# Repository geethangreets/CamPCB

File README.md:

# Hardware Development of Illumination and Sensor Board for Multispectral Cameras System 
This project is about hardware development for a vital sign detection device

This is a device that allows patients to take images of wounds at their homes with a higher frequency compared to typical hospital visits. The images would then be made available to their clinicians for continuous wound monitoring.

System Diagram:

3D rendering of the assembly:

Final PCB rendering front and back

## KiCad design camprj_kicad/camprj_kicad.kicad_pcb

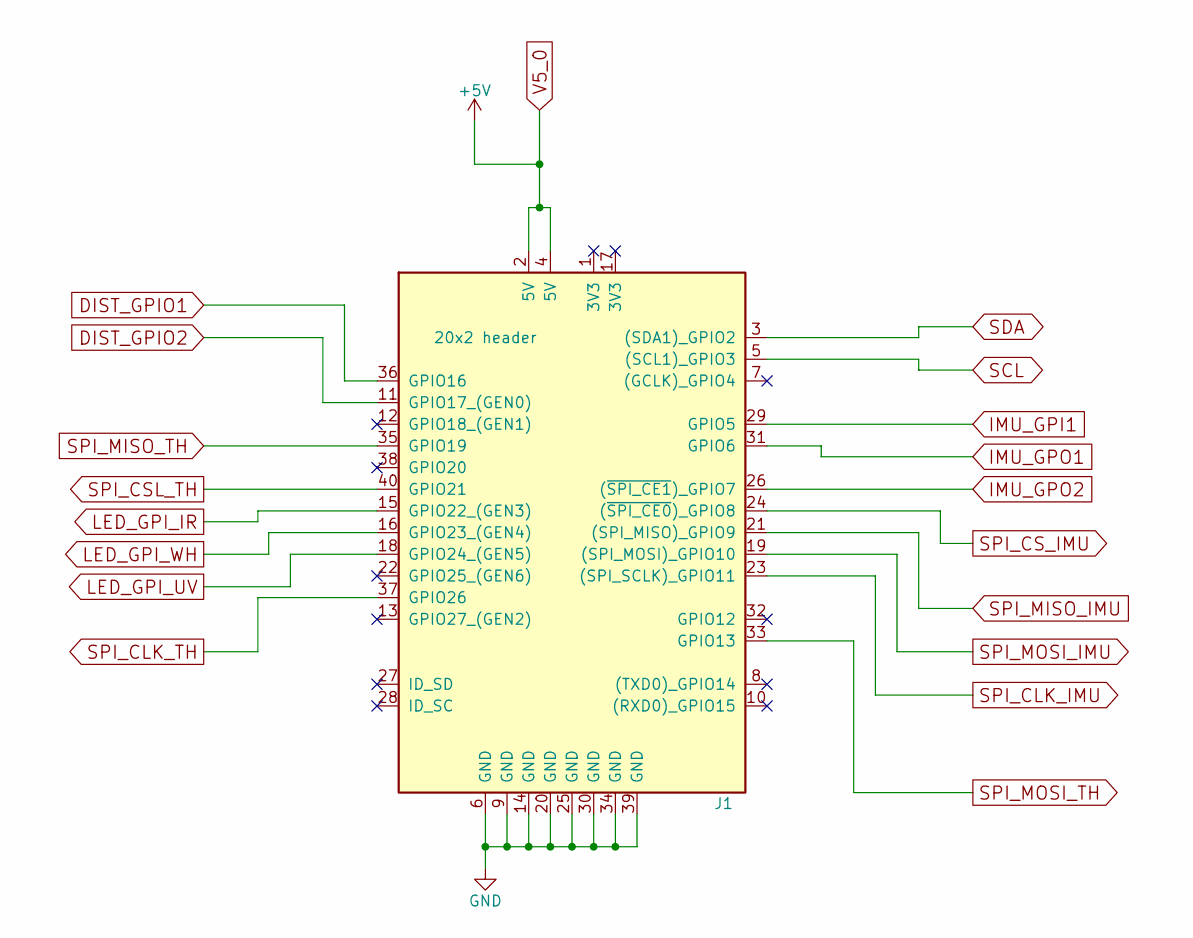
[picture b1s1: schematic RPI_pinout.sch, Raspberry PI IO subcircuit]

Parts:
J1: 20x2 header; Pin_Header_Straight_2x20_Pitch2.54mm; MPN ESQ-120-69-G-D-LL

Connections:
DIST_GPIO1: J1.36 (GPIO16); also elsewhere on the board
DIST_GPIO2: J1.11 (GPIO17_(GEN0)); also elsewhere on the board
GND: J1.6 (GND), J1.9 (GND), J1.14 (GND), J1.20 (GND), J1.25 (GND), J1.30 (GND), J1.34 (GND), J1.39 (GND); also elsewhere on the board
IMU_GPI1: J1.29 (GPIO5); also elsewhere on the board
IMU_GPO1: J1.31 (GPIO6); also elsewhere on the board
IMU_GPO2: J1.26 ((~SPI_CE1~)_GPIO7); also elsewhere on the board
LED_GPI_IR: J1.15 (GPIO22_(GEN3)); also elsewhere on the board
LED_GPI_UV: J1.18 (GPIO24_(GEN5)); also elsewhere on the board
LED_GPI_WH: J1.16 (GPIO23_(GEN4)); also elsewhere on the board
SCL: J1.5 ((SCL1)_GPIO3); also elsewhere on the board
SDA: J1.3 ((SDA1)_GPIO2); also elsewhere on the board
SPI_CLK_IMU: J1.23 ((SPI_SCLK)_GPIO11); also elsewhere on the board
SPI_CLK_TH: J1.37 (GPIO26); also elsewhere on the board
SPI_CSL_TH: J1.40 (GPIO21); also elsewhere on the board
SPI_CS_IMU: J1.24 ((~SPI_CE0~)_GPIO8); also elsewhere on the board
SPI_MISO_IMU: J1.21 ((SPI_MISO)_GPIO9); also elsewhere on the board
SPI_MISO_TH: J1.35 (GPIO19); also elsewhere on the board
SPI_MOSI_IMU: J1.19 ((SPI_MOSI)_GPIO10); also elsewhere on the board
SPI_MOSI_TH: J1.33 (GPIO13); also elsewhere on the board
V5_0: J1.2 (5V), J1.4 (5V); also elsewhere on the board

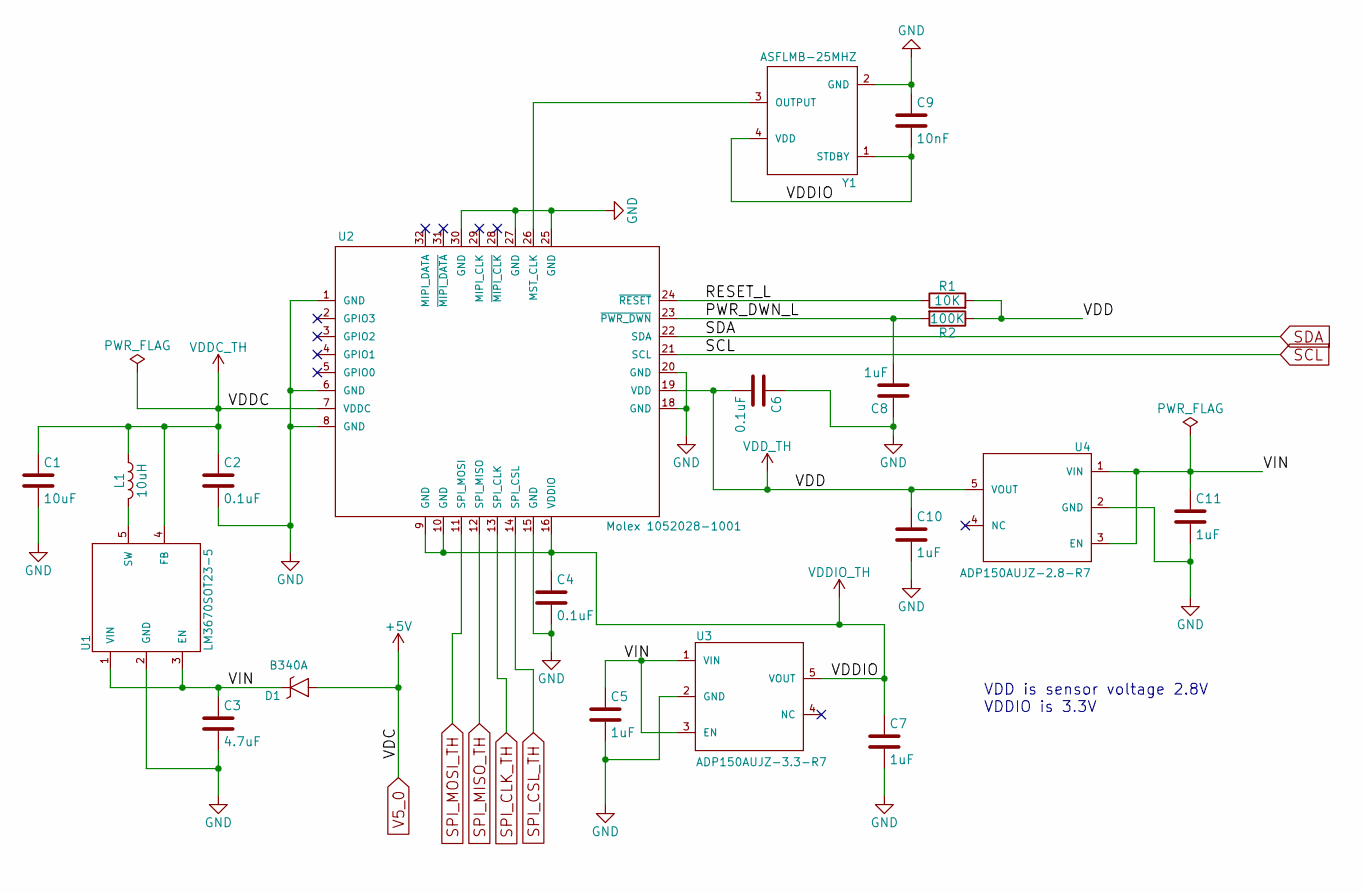
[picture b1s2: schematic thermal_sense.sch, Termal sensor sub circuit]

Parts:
C1: 10uF; C_0603_HandSoldering
C2, C4, C6: 0.1uF; C_0603_HandSoldering
C3: 4.7uF; C_0603_HandSoldering
C5, C7, C8, C10, C11: 1uF; C_0603_HandSoldering
C9: 10nF; C_0603_HandSoldering
D1: B340A; D_SMA_Handsoldering_AC; MPN B340A-13-F
L1: 10uH; L_1210_HandSoldering
R1: 10K; R_0603_HandSoldering
R2: 100K; R_0603_HandSoldering
U1: LM3670SOT23-5; SOT-23-5_HandSoldering; MPN LM3670MFX-ADJ/NOPB
U2: Molex 1052028-1001; 105028-1001; MPN 105028-1001
U3: ADP150AUJZ-3.3-R7; TSOT-23-5_HandSoldering; MPN ADP150AUJZ-3.3-R7
U4: ADP150AUJZ-2.8-R7; TSOT-23-5_HandSoldering; MPN ADP150AUJZ-2.8-R7
Y1: ASFLMB-25MHZ; 5X3.2-CRYSTAL; MPN ASFLMB-25.000MHZ-LC-T

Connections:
/thermal_sense/PWR_DWN_L: C8.2, R2.2, U2.23 (~PWR_DWN)
/thermal_sense/RESET_L: R1.1, U2.24 (~RESET)
/thermal_sense/VIN: C3.1, C5.1, C11.1, D1.C, U1.1 (VIN), U1.3 (EN), U3.1 (VIN), U3.3 (EN), U4.1 (VIN), U4.3 (EN)
GND: C1.2, C2.2, C3.2, C4.2, C5.2, C6.1, C7.2, C8.1, C9.1, C10.2, C11.2, U1.2 (GND), U2.1 (GND), U2.6 (GND), U2.8 (GND), U2.15 (GND), U2.18 (GND), U2.20 (GND), U2.25 (GND), U2.27 (GND), U2.30 (GND), U3.2 (GND), U4.2 (GND), Y1.2 (GND); also elsewhere on the board
unnamed: L1.2, U1.5 (SW)
unnamed: U2.26 (MST_CLK), Y1.3 (OUTPUT)
SCL: U2.21 (SCL); also elsewhere on the board
SDA: U2.22 (SDA); also elsewhere on the board
SPI_CLK_TH: U2.13 (SPI_CLK); also elsewhere on the board
SPI_CSL_TH: U2.14 (SPI_CSL); also elsewhere on the board
SPI_MISO_TH: U2.12 (SPI_MISO); also elsewhere on the board
SPI_MOSI_TH: U2.11 (SPI_MOSI); also elsewhere on the board
V5_0: D1.A; also elsewhere on the board
VDDC_TH: C1.1, C2.1, L1.1, U1.4 (FB), U2.7 (VDDC)
VDDIO_TH: C4.1, C7.1, C9.2, U2.9 (GND), U2.10 (GND), U2.16 (VDDIO), U3.5 (VOUT), Y1.1 (STDBY), Y1.4 (VDD)
VDD_TH: C6.2, C10.1, R1.2, R2.1, U2.19 (VDD), U4.5 (VOUT)

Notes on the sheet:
VDD is sensor voltage 2.8V VDDIO is 3.3V

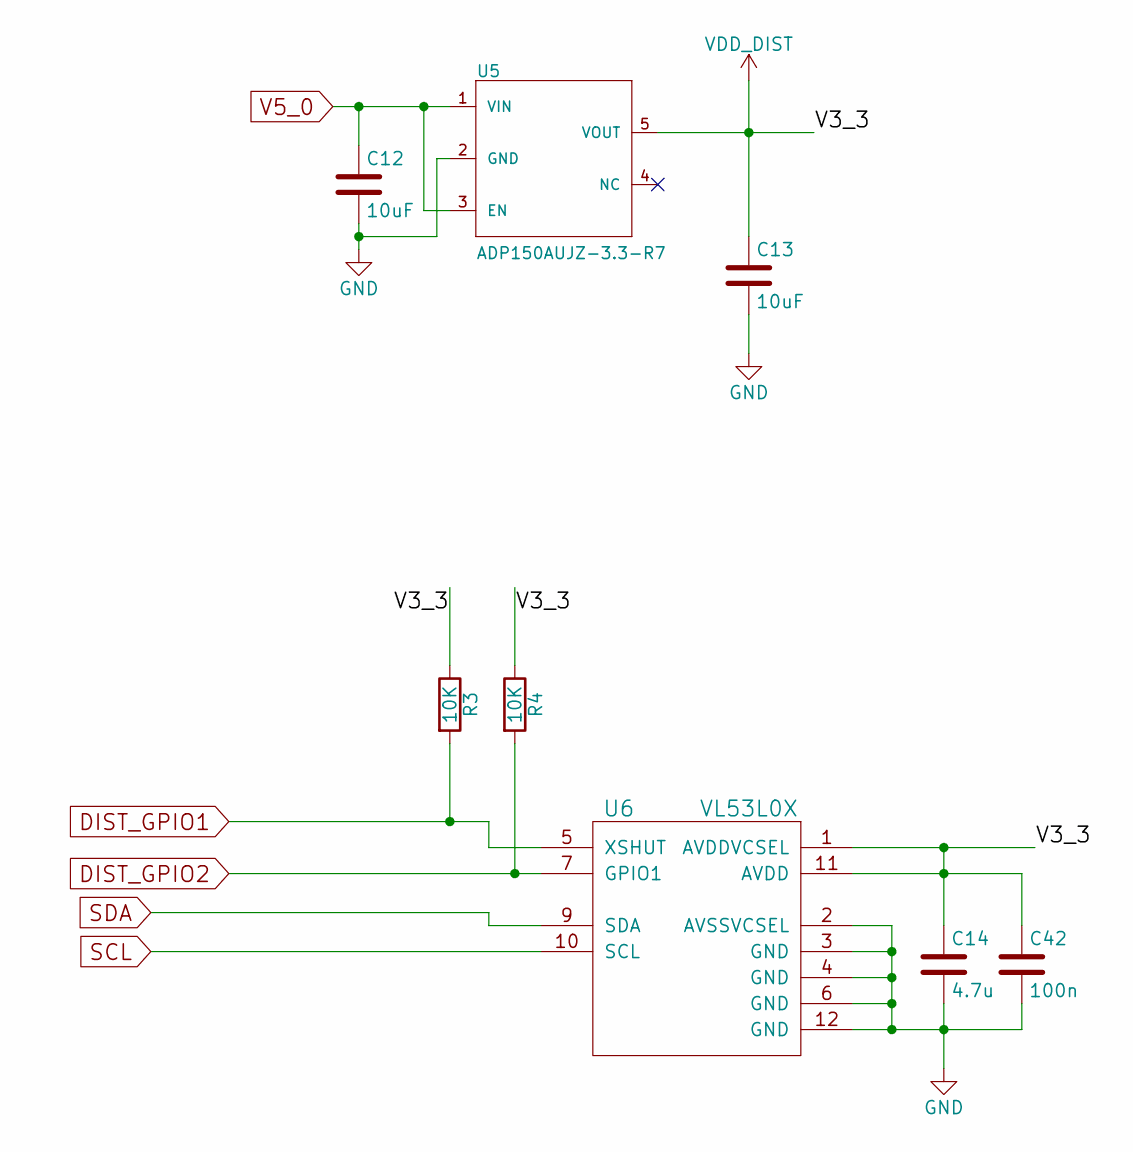
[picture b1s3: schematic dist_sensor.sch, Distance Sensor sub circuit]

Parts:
C12, C13: 10uF; C_0603_HandSoldering
C14: 4.7u; C_0603_HandSoldering
C42: 100n; C_0603_HandSoldering
R3, R4: 10K; R_0603_HandSoldering
U5: ADP150AUJZ-3.3-R7; TSOT-23-5_HandSoldering; MPN ADP150AUJZ-3.3-R7
U6: VL53L0X; Optical_LGA12; MPN VL53L0CXV0DH/1

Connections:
DIST_GPIO1: R3.2, U6.5 (XSHUT); also elsewhere on the board
DIST_GPIO2: R4.2, U6.7 (GPIO1); also elsewhere on the board
GND: C12.2, C13.2, C14.2, C42.2, U5.2 (GND), U6.2 (AVSSVCSEL), U6.3 (GND), U6.4 (GND), U6.6 (GND), U6.12 (GND); also elsewhere on the board
SCL: U6.10 (SCL); also elsewhere on the board
SDA: U6.9 (SDA); also elsewhere on the board
V5_0: C12.1, U5.1 (VIN), U5.3 (EN); also elsewhere on the board
VDD_DIST: C13.1, C14.1, C42.1, R3.1, R4.1, U5.5 (VOUT), U6.1 (AVDDVCSEL), U6.11 (AVDD)

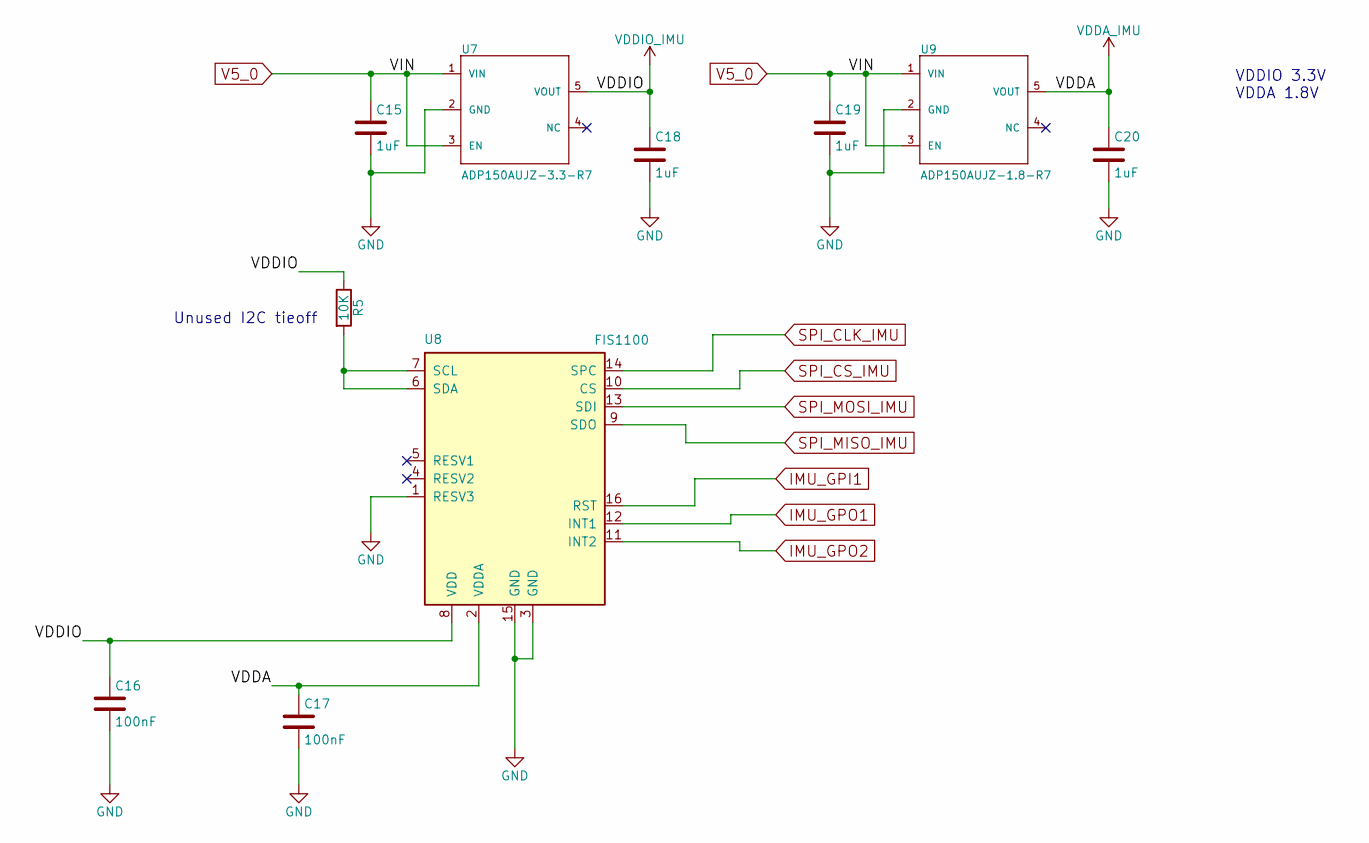
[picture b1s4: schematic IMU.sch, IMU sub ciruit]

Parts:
C15, C18, C19, C20: 1uF; C_0603_HandSoldering
C16, C17: 100nF; C_0603_HandSoldering
R5: 10K; R_0603_HandSoldering
U7: ADP150AUJZ-3.3-R7; TSOT-23-5_HandSoldering; MPN ADP150AUJZ-3.3-R7
U8: FIS1100; LGA16; MPN FIS1100
U9: ADP150AUJZ-1.8-R7; TSOT-23-5_HandSoldering; MPN ADP150AUJZ-1.8-R7

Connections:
GND: C15.2, C16.2, C17.2, C18.2, C19.2, C20.2, U7.2 (GND), U8.1 (RESV3), U8.3 (GND), U8.15 (GND), U9.2 (GND); also elsewhere on the board
IMU_GPI1: U8.16 (RST); also elsewhere on the board
IMU_GPO1: U8.12 (INT1); also elsewhere on the board
IMU_GPO2: U8.11 (INT2); also elsewhere on the board
unnamed: R5.2, U8.6 (SDA), U8.7 (SCL)
SPI_CLK_IMU: U8.14 (SPC); also elsewhere on the board
SPI_CS_IMU: U8.10 (CS); also elsewhere on the board
SPI_MISO_IMU: U8.9 (SDO); also elsewhere on the board
SPI_MOSI_IMU: U8.13 (SDI); also elsewhere on the board
V5_0: C15.1, C19.1, U7.1 (VIN), U7.3 (EN), U9.1 (VIN), U9.3 (EN); also elsewhere on the board
VDDA_IMU: C17.1, C20.1, U8.2 (VDDA), U9.5 (VOUT)
VDDIO_IMU: C16.1, C18.1, R5.1, U7.5 (VOUT), U8.8 (VDD)

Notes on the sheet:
VDDIO 3.3V VDDA 1.8V
Unused I2C tieoff

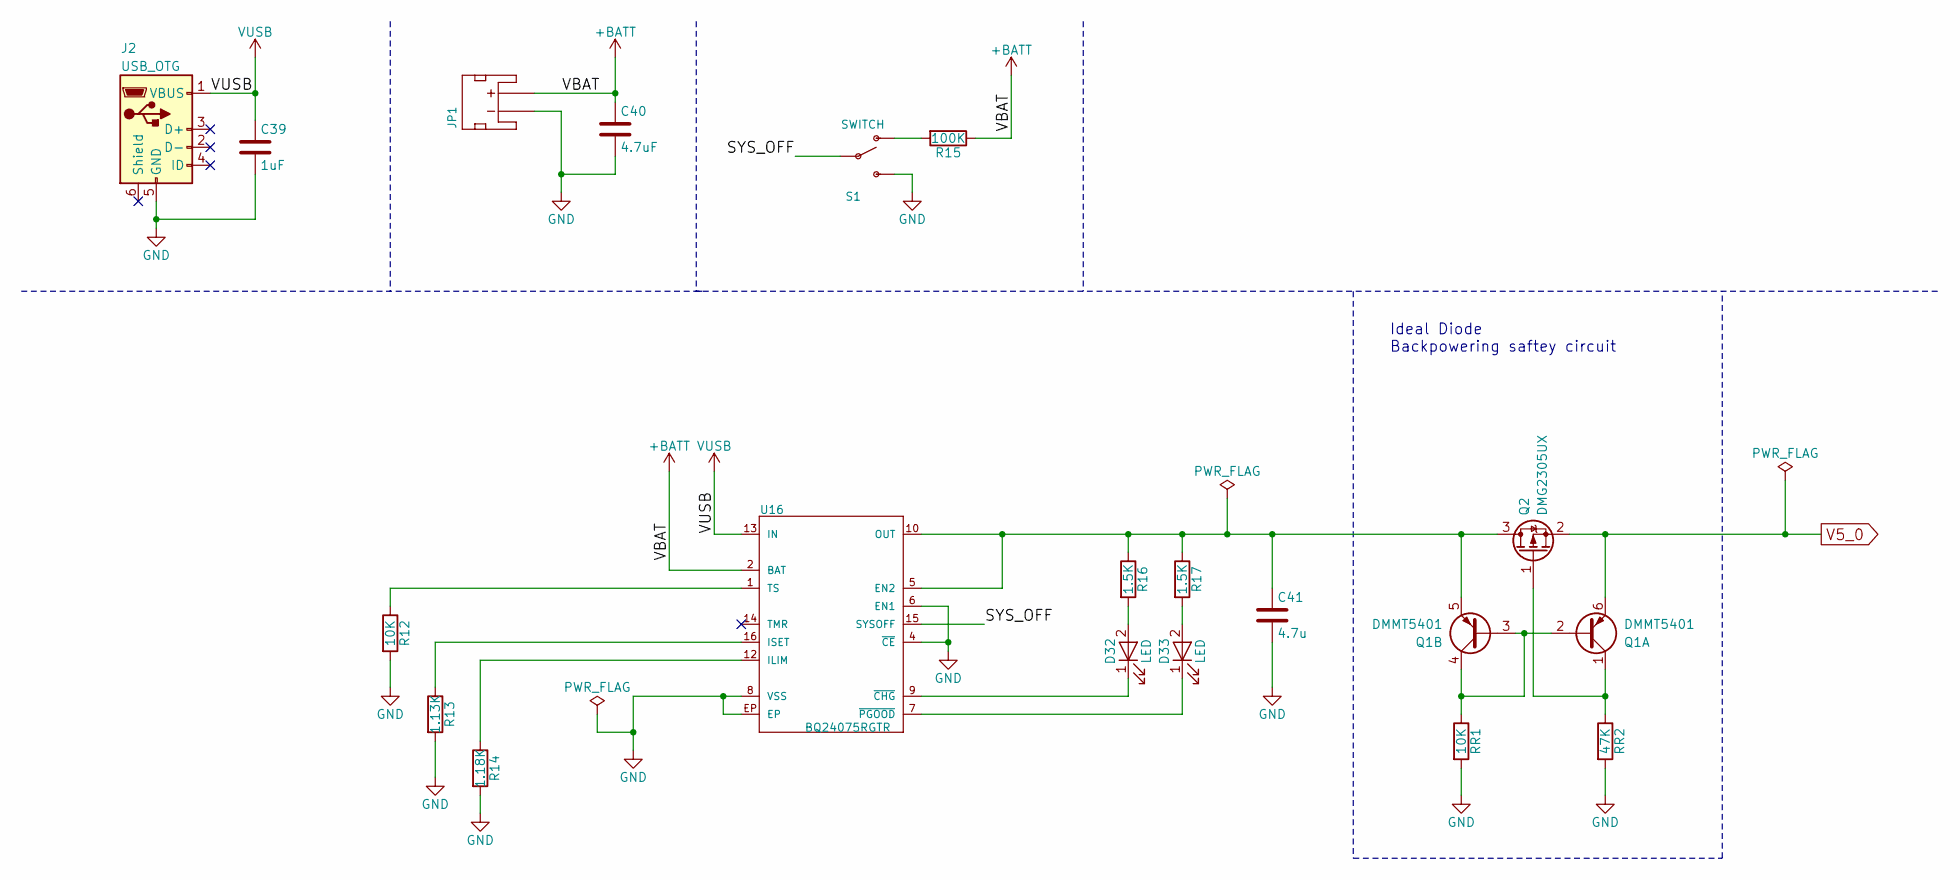
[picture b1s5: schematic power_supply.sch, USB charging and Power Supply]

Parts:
C39: 1uF; C_0603_HandSoldering
C40: 4.7uF; C_0603_HandSoldering
C41: 4.7u; C_0603_HandSoldering
D32, D33: LED; LED_PLCC-2
J2: USB_OTG; USB_Micro-B; MPN 629105150521
JP1: JST_2MM_MALE; JST_PH_B2B-PH-K_02x2.00mm_Straight; MPN BM02B-CPTK-1A-TB
Q1: DMMT5401; SOT-23-6_Handsoldering; MPN DMMT5401-7-F
Q2: DMG2305UX; SOT-23; MPN DMG2305UX-13
R12: 10K; R_0603_HandSoldering
R13: 1.13K; R_0603_HandSoldering
R14: 1.18K; R_0603_HandSoldering
R15: 100K; R_0603_HandSoldering
R16, R17: 1.5K; R_0603_HandSoldering
RR1: 10K; R_0603_HandSoldering
RR2: 47K; R_0603_HandSoldering
S1: SWITCH; DPST_TE_SSJ12R04; MPN 1825282-1
U16: BQ24075RGTR; QFN-16-1EP_3x3mm_Pitch0.5mm; MPN BQ24075RGTR

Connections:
+BATT: C40.1, JP1.2 (+), R15.1, U16.2 (BAT), U16.3 (BAT)
/power_supply/SYS_OFF: S1.2, U16.15 (SYSOFF)
GND: C39.2, C40.2, C41.2, J2.5 (GND), JP1.1 (-), R12.2, R13.2, R14.2, RR1.2, RR2.2, S1.3 (S), U16.4 (~CE~), U16.6 (EN1), U16.8 (VSS), U16.EP; also elsewhere on the board
unnamed: C41.1, Q1.5 (E2), Q2.3 (D), R16.1, R17.1, U16.5 (EN2), U16.10 (OUT), U16.11 (OUT)
unnamed: D32.1 (K), U16.9 (~CHG~)
unnamed: D32.2 (A), R16.2
unnamed: D33.1 (K), U16.7 (~PGOOD~)
unnamed: D33.2 (A), R17.2
unnamed: Q1.1 (C1), Q2.1 (G), RR2.1
unnamed: Q1.2 (B1), Q1.3 (B2), Q1.4 (C2), RR1.1
unnamed: R12.1, U16.1 (TS)
unnamed: R13.1, U16.16 (ISET)
unnamed: R14.1, U16.12 (ILIM)
unnamed: R15.2, S1.1 (O)
V5_0: Q1.6 (E1), Q2.2 (S); also elsewhere on the board
VUSB: C39.1, J2.1 (VBUS), U16.13 (IN)

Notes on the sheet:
Ideal Diode Backpowering saftey circuit

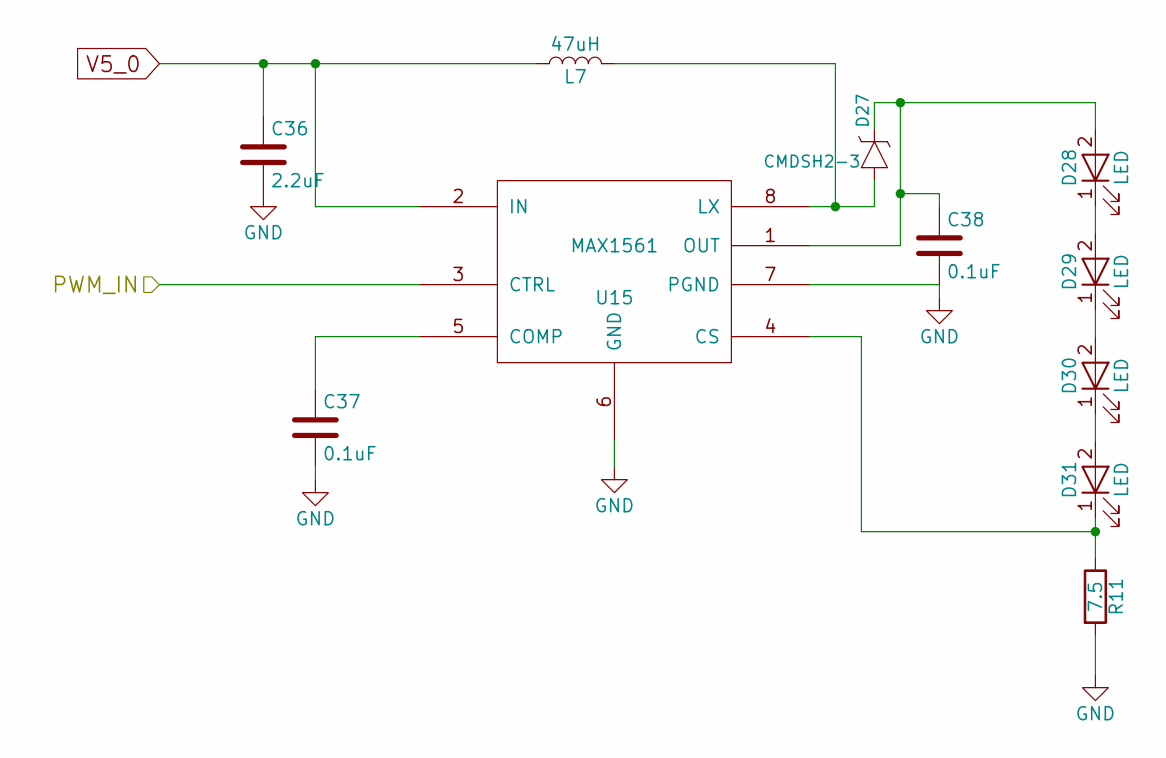
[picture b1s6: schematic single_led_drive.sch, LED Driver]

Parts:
C24: 2.2uF; C_0603_HandSoldering
C25, C26: 0.1uF; C_0603_HandSoldering
D8, D9, D10, D11: LED; LED_PLCC-2
D12: CMDSH2-3; D_SOD-323_HandSoldering; MPN CMDSH2-3 TR
L3: 47uH; L_1210_HandSoldering
R7: 7.5; R_0603_HandSoldering
U11: MAX1561; 8-TDFN-EP; MPN MAX1561ETA+T

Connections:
GND: C24.2, C25.2, C26.2, R7.2, U11.6 (GND), U11.7 (PGND), U11.9 (EP); also elsewhere on the board
LED_GPI_IR: U11.3 (CTRL); also elsewhere on the board
unnamed: C25.1, U11.5 (COMP)
unnamed: D8.1 (K), D9.2 (A)
unnamed: D10.1 (K), D11.2 (A)
unnamed: D9.1 (K), D10.2 (A)
unnamed: D11.1 (K), R7.1, U11.4 (CS)
V5_0: C24.1, L3.1, U11.2 (IN); also elsewhere on the board

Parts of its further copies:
C21, C27, C30, C33, C36: 2.2uF; C_0603_HandSoldering
C22, C23, C28, C29, C31, C32, C34, C35, C37, C38: 0.1uF; C_0603_HandSoldering
D2, D7, D17, D22, D27: CMDSH2-3; D_SOD-323_HandSoldering; MPN CMDSH2-3 TR
D3, D4, D5, D6, D13, D14, D15, D16, D18, D19, D20, D21, D23, D24, D25, D26, D28, D29, D30, D31: LED; LED_PLCC-2
L2, L4, L5, L6, L7: 47uH; L_1210_HandSoldering
R6, R8, R9, R10, R11: 7.5; R_0603_HandSoldering
U10, U12, U13, U14, U15: MAX1561; 8-TDFN-EP; MPN MAX1561ETA+T

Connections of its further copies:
/LED_Drive/IR_SET3/PWM_IN: U12.3 (CTRL)
GND: C21.2, C22.2, C23.2, C27.2, C28.2, C29.2, C30.2, C31.2, C32.2, C33.2, C34.2, C35.2, C36.2, C37.2, C38.2, R6.2, R8.2, R9.2, R10.2, R11.2, U10.6 (GND), U10.7 (PGND), U10.9 (EP), U12.6 (GND), U12.7 (PGND), U12.9 (EP), U13.6 (GND), U13.7 (PGND), U13.9 (EP), U14.6 (GND), U14.7 (PGND), U14.9 (EP), U15.6 (GND), U15.7 (PGND), U15.9 (EP); also elsewhere on the board
LED_GPI_IR: U10.3 (CTRL), U13.3 (CTRL); also elsewhere on the board
LED_GPI_UV: U15.3 (CTRL); also elsewhere on the board
LED_GPI_WH: U14.3 (CTRL); also elsewhere on the board
unnamed: C22.1, U10.5 (COMP)
unnamed: C23.1, D2.2, D3.2 (A), U10.1 (OUT)
unnamed: C28.1, U12.5 (COMP)
unnamed: C31.1, U13.5 (COMP)
unnamed: C32.1, D17.2, D18.2 (A), U13.1 (OUT)
unnamed: C34.1, U14.5 (COMP)
unnamed: C35.1, D22.2, D23.2 (A), U14.1 (OUT)
unnamed: C37.1, U15.5 (COMP)
unnamed: C38.1, D27.2, D28.2 (A), U15.1 (OUT)
unnamed: D2.1, L2.2, U10.8 (LX)
unnamed: D3.1 (K), D4.2 (A)
unnamed: D4.1 (K), D5.2 (A)
unnamed: D5.1 (K), D6.2 (A)
unnamed: D6.1 (K), R6.1, U10.4 (CS)
unnamed: D13.1 (K), D14.2 (A)
unnamed: D14.1 (K), D15.2 (A)
unnamed: D15.1 (K), D16.2 (A)
unnamed: D16.1 (K), R8.1, U12.4 (CS)
unnamed: D17.1, L5.2, U13.8 (LX)
unnamed: D18.1 (K), D19.2 (A)
unnamed: D19.1 (K), D20.2 (A)
unnamed: D20.1 (K), D21.2 (A)
unnamed: D21.1 (K), R9.1, U13.4 (CS)
unnamed: D22.1, L6.2, U14.8 (LX)
unnamed: D23.1 (K), D24.2 (A)
unnamed: D24.1 (K), D25.2 (A)
unnamed: D25.1 (K), D26.2 (A)
unnamed: D26.1 (K), R10.1, U14.4 (CS)
unnamed: D27.1, L7.2, U15.8 (LX)
unnamed: D28.1 (K), D29.2 (A)
unnamed: D29.1 (K), D30.2 (A)
unnamed: D30.1 (K), D31.2 (A)
unnamed: D31.1 (K), R11.1, U15.4 (CS)
V5_0: C21.1, C27.1, C30.1, C33.1, C36.1, L2.1, L4.1, L5.1, L6.1, L7.1, U10.2 (IN), U12.2 (IN), U13.2 (IN), U14.2 (IN), U15.2 (IN); also elsewhere on the board

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
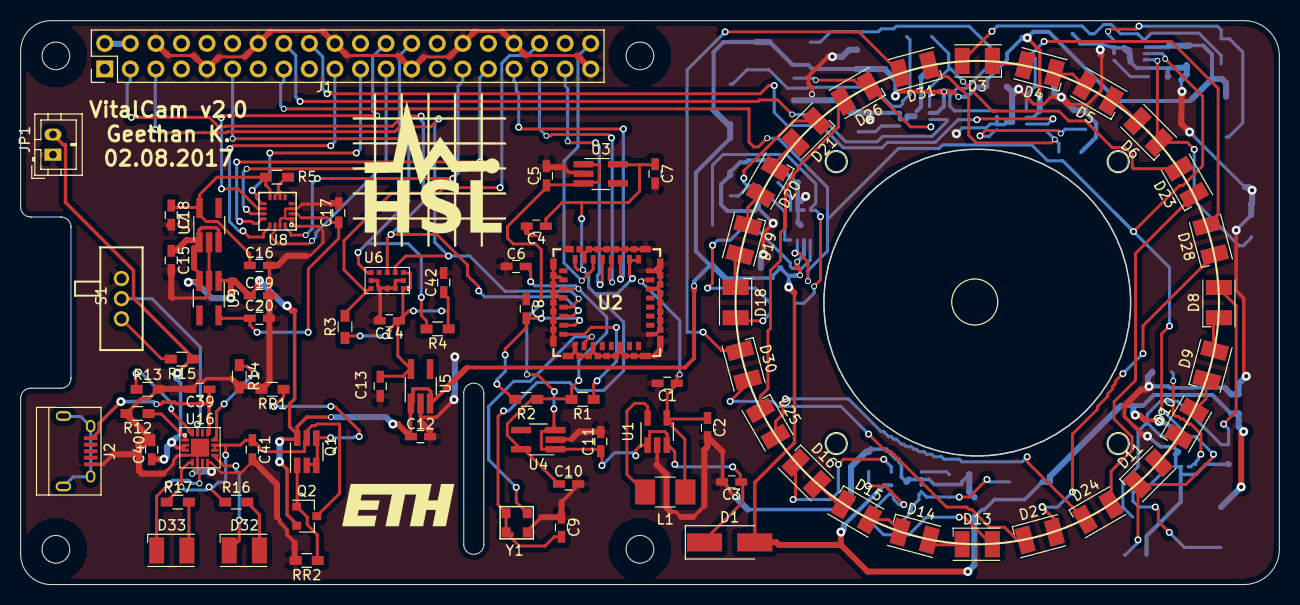
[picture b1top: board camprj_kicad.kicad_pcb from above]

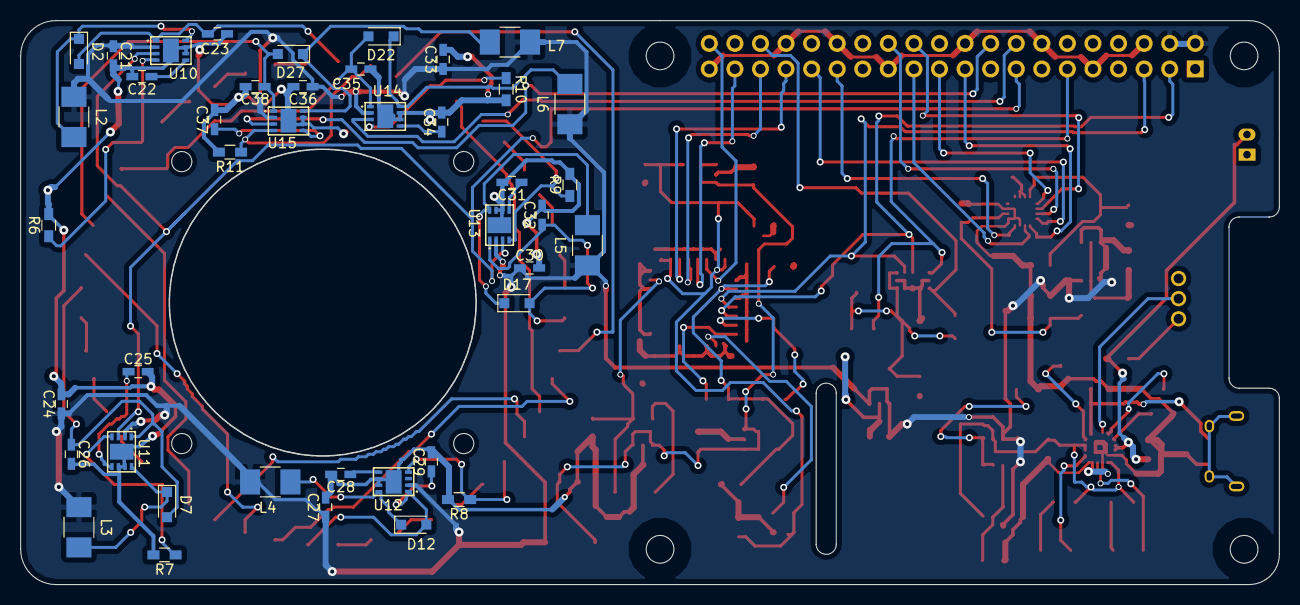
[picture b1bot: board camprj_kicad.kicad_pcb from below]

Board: 2 copper layers, 125.0 x 56.0 mm, 124 parts (42 on the bottom side), 88 nets.

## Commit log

2017-07-20 Adding docs
2017-07-20 More docs
2017-07-20 3D model and some other files
2017-07-20 Adding KiCAD PCB project
2017-07-23 Board design: component placement done
2017-07-26 main system image added
2017-07-27 routing done
2017-08-02 Final Delivery
2017-08-03 Logos updated
2017-08-03 Readme updated
2017-08-03 README.md edited online with Bitbucket
2017-08-03 fixing pathnames
